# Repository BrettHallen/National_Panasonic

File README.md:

# National/Panasonic
Information about National/Panasonic computers.

## [National JR-200](/National_JR-200)

## [National CF-3000](/National_CF-3000)
The MSX1 compatible computer.<br>

Machines in the range:<br>
- National CF-2000 (all-in-one)
- National CF-2601 (Superimposition Unit)
- National CF-3000 (separate keyboard)
- National CF-3300 (with additional 3.5" floppy drive)

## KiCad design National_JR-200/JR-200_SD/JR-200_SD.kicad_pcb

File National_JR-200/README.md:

# National JR-200
Information about the National/Panasonic JR-200 computer.<br>

It was exported to the US as the JR-200U and Europe as the JR-200UP (PAL).<br>

# Troubleshooting Φ2 Clock
My first JR-200 doesn't work - the Φ2 is currently missing.

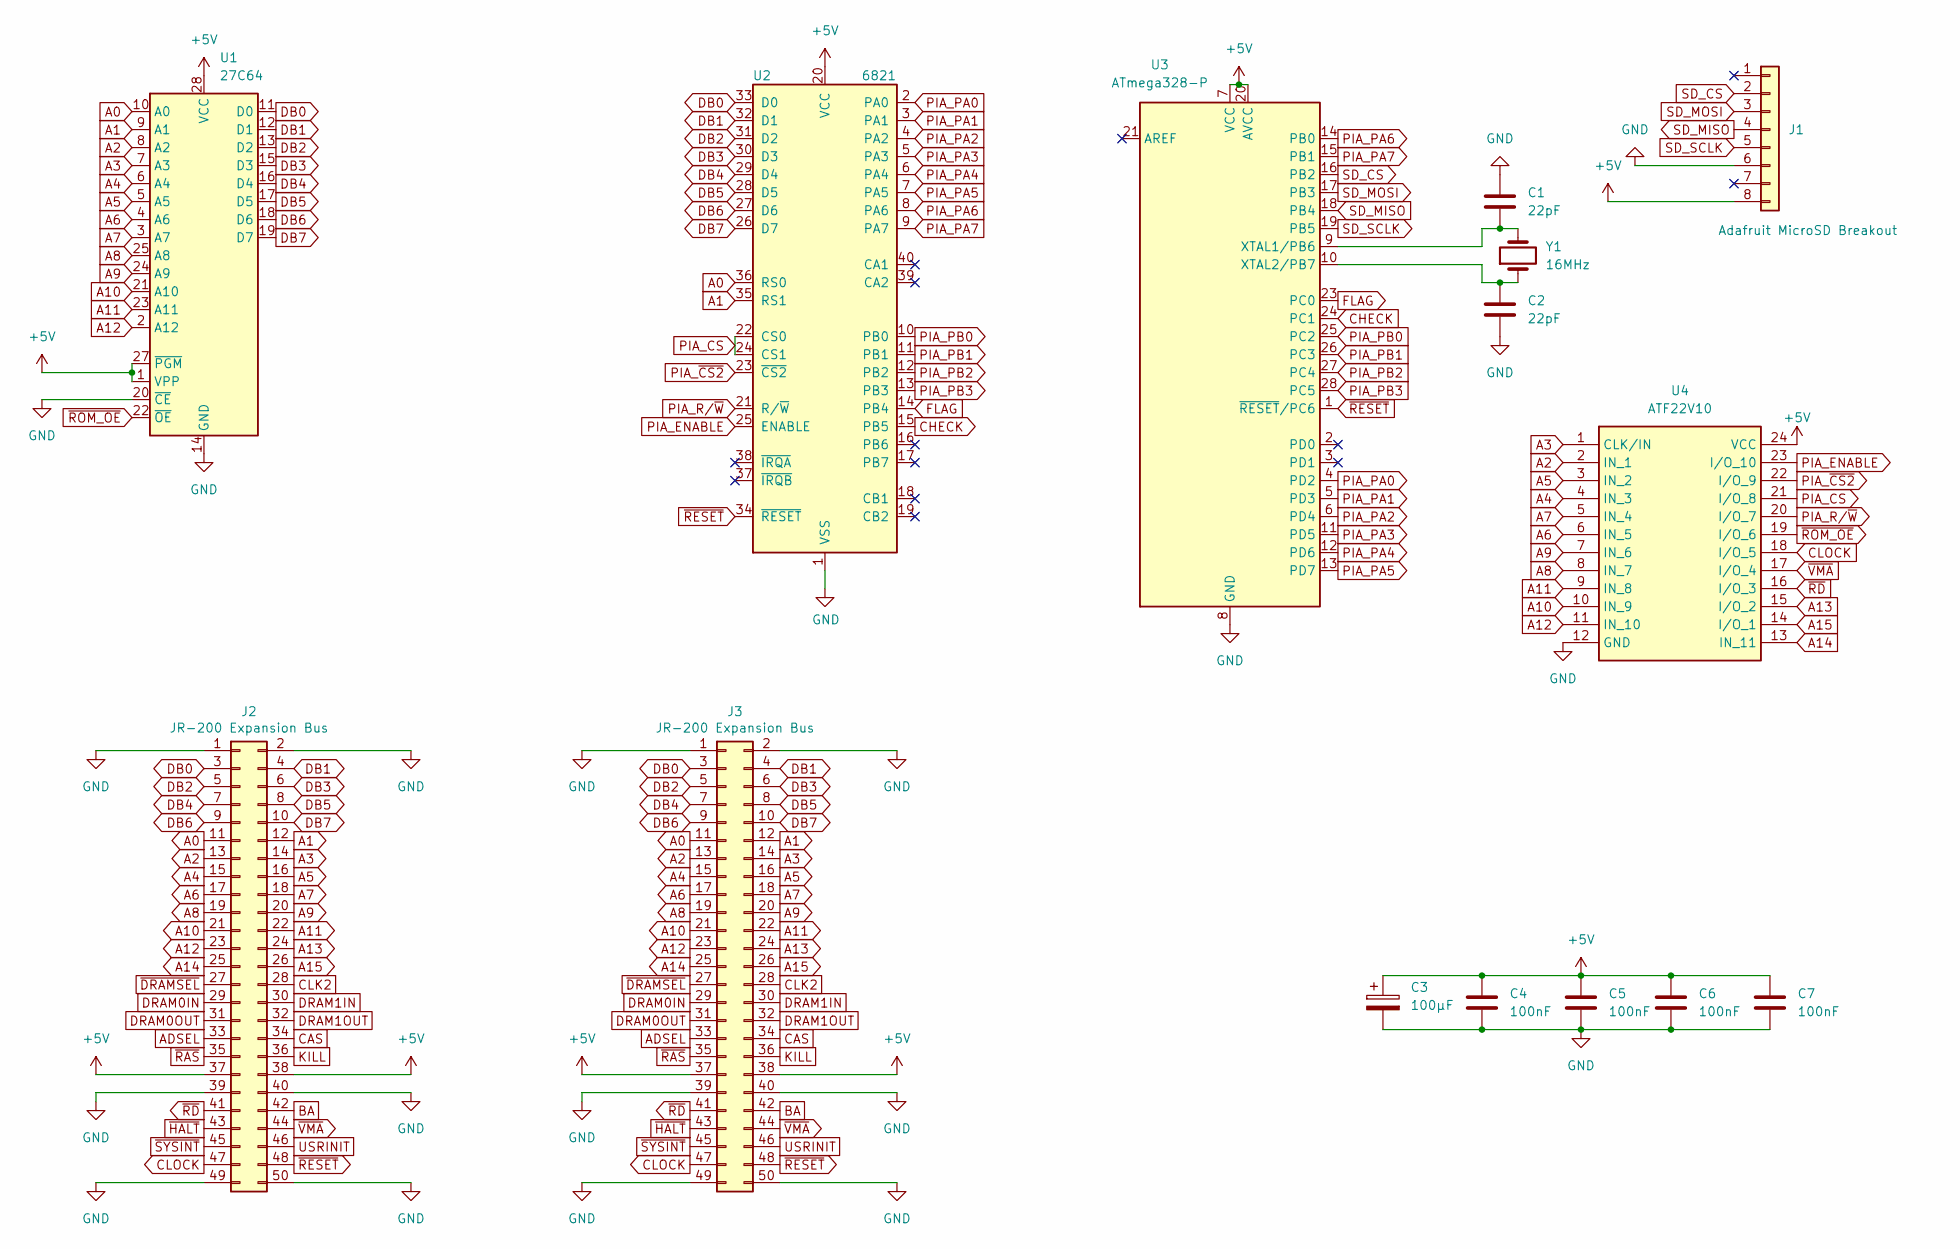
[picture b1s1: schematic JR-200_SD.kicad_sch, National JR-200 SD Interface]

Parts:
C1, C2: 22pF; C_Disc_D3.8mm_W2.6mm_P2.50mm
C3: 100µF; CP_Radial_D5.0mm_P2.50mm
C4, C5, C6, C7: 100nF; C_Disc_D3.8mm_W2.6mm_P2.50mm
J1: Adafruit MicroSD Breakout
J2, J3: JR-200 Expansion Bus; PinHeader_2x25_P2.54mm_Vertical
U1: 27C64; DIP-28_W15.24mm
U2: 6821; DIP-40_W15.24mm_LongPads
U3: ATmega328-P; DIP-28_W7.62mm
U4: ATF22V10; DIP-24_W7.62mm; Mouser Part Number 556-AF750CL15PU
Y1: 16MHz; Crystal_HC49-U_Vertical

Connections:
+5V: C3.1, C4.1, C5.1, C6.1, C7.1, J1.8, J2.37, J2.38, J3.37, J3.38, U1.1 (VPP), U1.27 (~PGM), U1.28 (VCC), U2.20 (VCC), U3.7 (VCC), U3.20 (AVCC), U4.24 (VCC)
A0: J2.11, J3.11, U1.10 (A0), U2.36 (RS0)
A1: J2.12, J3.12, U1.9 (A1), U2.35 (RS1)
A2: J2.13, J3.13, U1.8 (A2), U4.2 (IN_1)
A3: J2.14, J3.14, U1.7 (A3), U4.1 (CLK/IN)
A4: J2.15, J3.15, U1.6 (A4), U4.4 (IN_3)
A5: J2.16, J3.16, U1.5 (A5), U4.3 (IN_2)
A6: J2.17, J3.17, U1.4 (A6), U4.6 (IN_5)
A7: J2.18, J3.18, U1.3 (A7), U4.5 (IN_4)
A8: J2.19, J3.19, U1.25 (A8), U4.8 (IN_7)
A9: J2.20, J3.20, U1.24 (A9), U4.7 (IN_6)
A10: J2.21, J3.21, U1.21 (A10), U4.10 (IN_9)
A11: J2.22, J3.22, U1.23 (A11), U4.9 (IN_8)
A12: J2.23, J3.23, U1.2 (A12), U4.11 (IN_10)
A13: J2.24, J3.24, U4.15 (I/O_2)
A14: J2.25, J3.25, U4.13 (IN_11)
A15: J2.26, J3.26, U4.14 (I/O_1)
ADSEL: J2.33, J3.33
BA: J2.42, J3.42
CAS: J2.34, J3.34
CHECK: U2.15 (PB5), U3.24 (PC1)
CLK2: J2.28, J3.28
CLOCK: J2.47, J3.47, U4.18 (I/O_5)
DB0: J2.3, J3.3, U1.11 (D0), U2.33 (D0)
DB1: J2.4, J3.4, U1.12 (D1), U2.32 (D1)
DB2: J2.5, J3.5, U1.13 (D2), U2.31 (D2)
DB3: J2.6, J3.6, U1.15 (D3), U2.30 (D3)
DB4: J2.7, J3.7, U1.16 (D4), U2.29 (D4)
DB5: J2.8, J3.8, U1.17 (D5), U2.28 (D5)
DB6: J2.9, J3.9, U1.18 (D6), U2.27 (D6)
DB7: J2.10, J3.10, U1.19 (D7), U2.26 (D7)
DRAM0IN: J2.29, J3.29
DRAM0OUT: J2.31, J3.31
DRAM1IN: J2.30, J3.30
DRAM1OUT: J2.32, J3.32
FLAG: U2.14 (PB4), U3.23 (PC0)
GND: C1.1, C2.2, C3.2, C4.2, C5.2, C6.2, C7.2, J1.6, J2.1, J2.2, J2.39, J2.40, J2.49, J2.50, J3.1, J3.2, J3.39, J3.40, J3.49, J3.50, U1.14 (GND), U1.20 (~CE), U2.1 (VSS), U3.8 (GND), U3.22 (GND), U4.12 (GND)
KILL: J2.36, J3.36
unnamed: C1.2, U3.9 (XTAL1/PB6), Y1.2
unnamed: C2.1, U3.10 (XTAL2/PB7), Y1.1
PIA_CS: U2.22 (CS0), U2.24 (CS1), U4.21 (I/O_8)
PIA_ENABLE: U2.25 (ENABLE), U4.23 (I/O_10)
PIA_PA0: U2.2 (PA0), U3.4 (PD2)
PIA_PA1: U2.3 (PA1), U3.5 (PD3)
PIA_PA2: U2.4 (PA2), U3.6 (PD4)
PIA_PA3: U2.5 (PA3), U3.11 (PD5)
PIA_PA4: U2.6 (PA4), U3.12 (PD6)
PIA_PA5: U2.7 (PA5), U3.13 (PD7)
PIA_PA6: U2.8 (PA6), U3.14 (PB0)
PIA_PA7: U2.9 (PA7), U3.15 (PB1)
PIA_PB0: U2.10 (PB0), U3.25 (PC2)
PIA_PB1: U2.11 (PB1), U3.26 (PC3)
PIA_PB2: U2.12 (PB2), U3.27 (PC4)
PIA_PB3: U2.13 (PB3), U3.28 (PC5)
PIA_R/~W: U2.21 (R/~W), U4.20 (I/O_7)
PIA_~CS2: U2.23 (~CS2), U4.22 (I/O_9)
SD_CS: J1.2, U3.16 (PB2)
SD_MISO: J1.4, U3.18 (PB4)
SD_MOSI: J1.3, U3.17 (PB3)
SD_SCLK: J1.5, U3.19 (PB5)
USRINIT: J2.46, J3.46
~DRAMSEL: J2.27, J3.27
~HALT: J2.43, J3.43
~RAS: J2.35, J3.35
~RD: J2.41, J3.41, U4.16 (I/O_3)
~RESET: J2.48, J3.48, U2.34 (~RESET), U3.1 (~RESET/PC6)
~ROM_OE: U1.22 (~OE), U4.19 (I/O_6)
~SYSINT: J2.45, J3.45
~VMA: J2.44, J3.44, U4.17 (I/O_4)

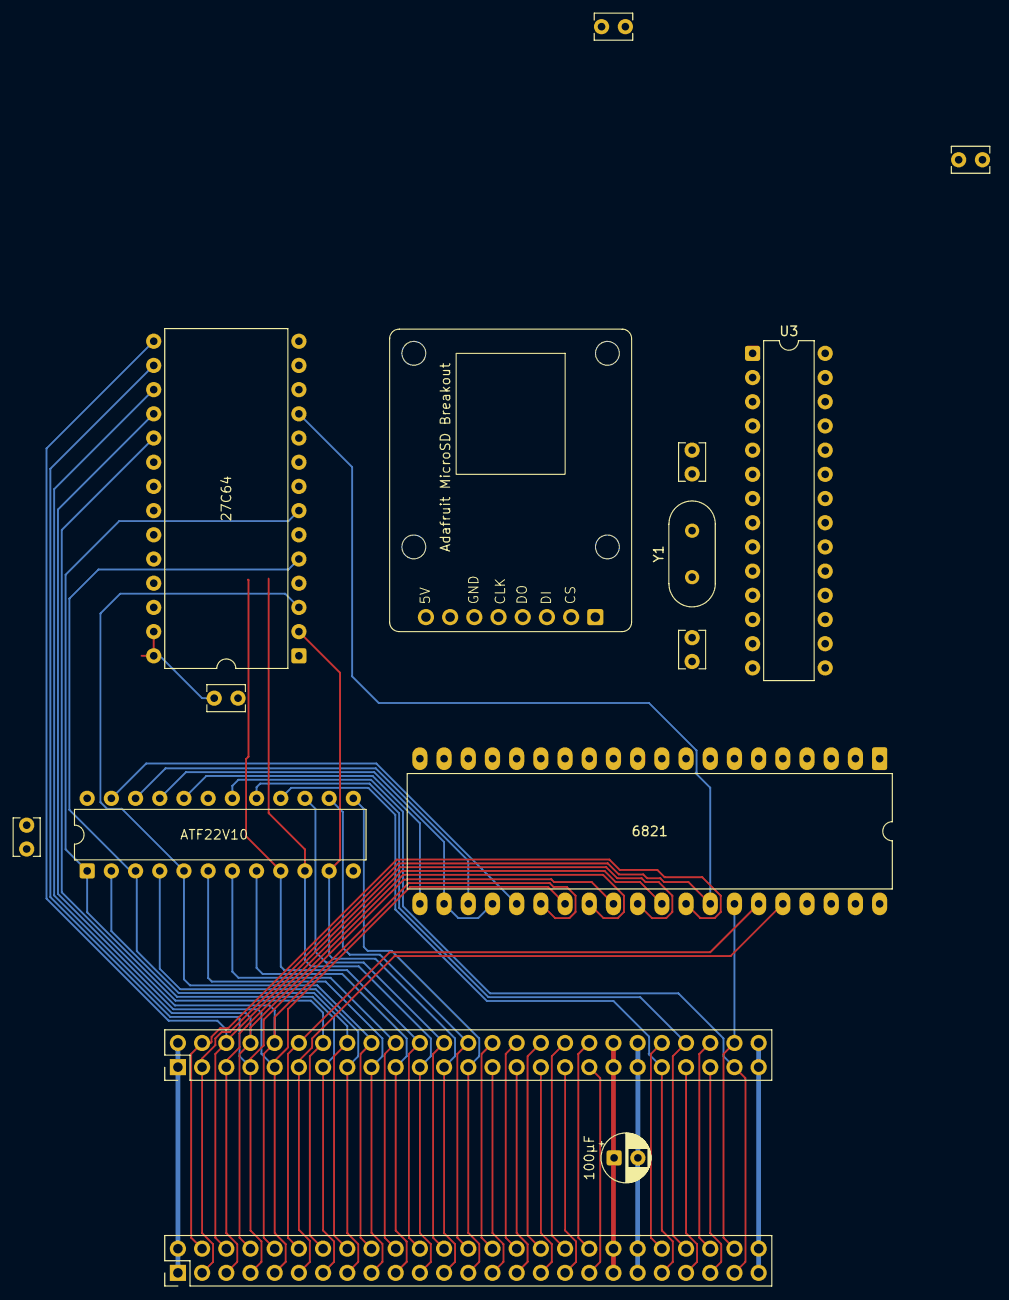
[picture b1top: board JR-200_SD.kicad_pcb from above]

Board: 2 copper layers, 15 parts (0 on the bottom side), 69 nets.

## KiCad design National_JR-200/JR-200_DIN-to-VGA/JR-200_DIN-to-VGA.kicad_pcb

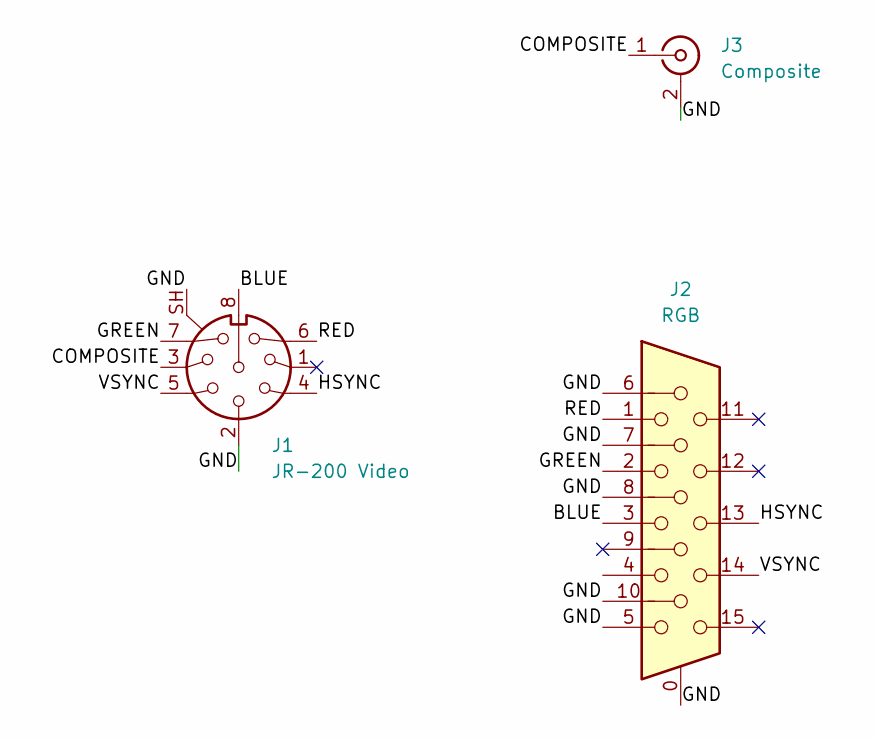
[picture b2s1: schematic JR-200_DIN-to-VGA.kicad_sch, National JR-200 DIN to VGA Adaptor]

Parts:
J1: JR-200 Video; SDF80J
J2: RGB; DSUB-15-HD_Socket_Horizontal_P2.29x2.54mm_EdgePinOffset8.35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
J3: Composite; 1560099E

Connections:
/BLUE: J1.8, J2.3
/COMPOSITE: J1.3, J3.1 (In)
/GND: J1.2, J1.SH, J2.0, J2.5, J2.6, J2.7, J2.8, J2.10, J3.2 (Ext)
/GREEN: J1.7, J2.2
/HSYNC: J1.4, J2.13
/RED: J1.6, J2.1
/VSYNC: J1.5, J2.14

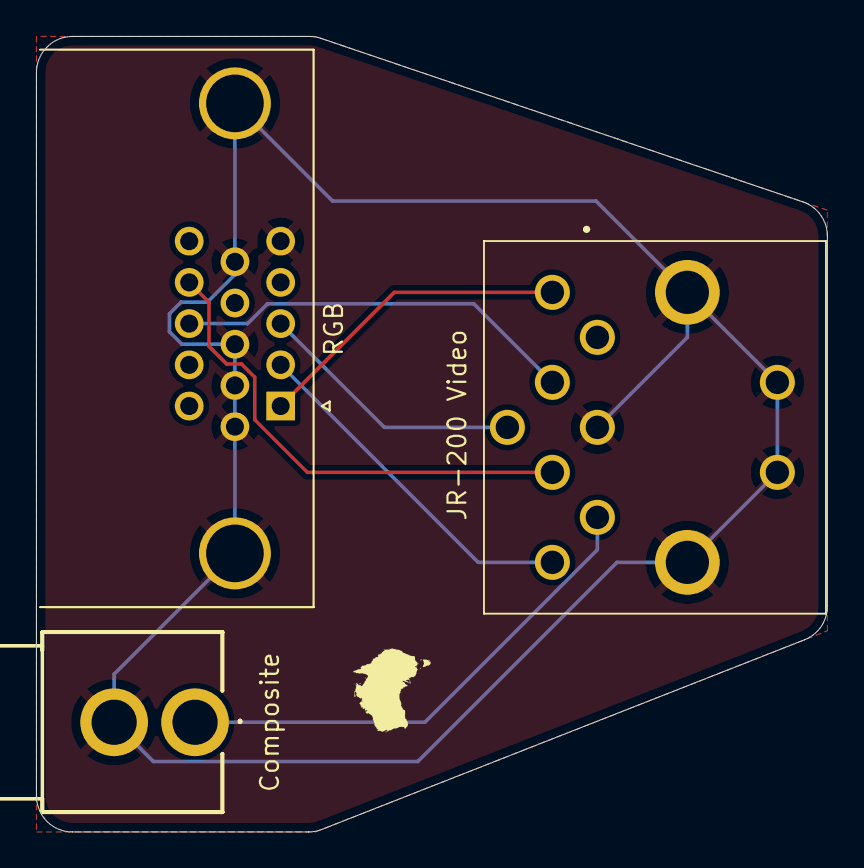
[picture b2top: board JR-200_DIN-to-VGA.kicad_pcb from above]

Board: 2 copper layers, 43.9 x 44.2 mm, 3 parts (0 on the bottom side), 7 nets.

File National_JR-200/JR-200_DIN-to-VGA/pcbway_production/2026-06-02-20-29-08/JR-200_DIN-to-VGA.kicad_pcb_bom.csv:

Designator,Quantity,Value,Footprint,Package,MPN,DNP,Mount_Type,Description
J1,1,JR-200 Video,SDF80J,,,,tht,
J2,1,RGB,DSUB-15-HD_Socket_Horizontal_P2.29x2.54mm_EdgePinOffset8.35mm_Housed_MountingHolesOffset10.89mm,,,,tht,"15-pin D-SUB connector, socket (female), High density (3 columns), Triple Row, Generic, VGA-connector, Mounting Hole"
J3,1,Composite,1560099E,,,,tht,"coaxial connector (BNC, SMA, SMB, SMC, Cinch/RCA, LEMO, ...)"

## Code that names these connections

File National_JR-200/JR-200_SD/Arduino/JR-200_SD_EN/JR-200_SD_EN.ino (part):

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/* 
ATmega328  Connection
--------------------
PB0        PIA PA6 (PIA_PA6)
PB1        PIA PA7 (PIA_PA7)
PB2        SD CS (CABLESELECTPIN)
PB3        SD MOSI
PB4        SD MISO
PB5        SD SCK
PC0        PIA PB4 (FLAGPIN)
PC1        PIA PB5 (CHKPIN)
PC2        PIA PB0 (PIA_PB0)
PC3        PIA PB1 (PIA_PB1)
PC4        PIA PB2 (PIA_PB2)
PC5        PIA PB3 (PIA_PB3)
PD2        PIA PA0 (PIA_PA0)
PD3        PIA PA1 (PIA_PA1)
PD4        PIA PA2 (PIA_PA2)
PD5        PIA PA3 (PIA_PA3)
PD6        PIA PA4 (PIA_PA4)
PD7        PIA PA5 (PIA_PA5)
*/
#define CABLESELECTPIN  (10)
#define CHKPIN          (15)
#define PIA_PA0          (2)
#define PIA_PA1          (3)
#define PIA_PA2          (4)
#define PIA_PA3          (5)
#define PIA_PA4          (6)
#define PIA_PA5          (7)
#define PIA_PA6          (8)
#define PIA_PA7          (9)
#define FLAGPIN         (14)
#define PIA_PB0         (16)
#define PIA_PB1         (17)
#define PIA_PB2         (18)
#define PIA_PB3         (19)

#define SD_STATUS_OK             0x00
#define SD_STATUS_INIT_ERROR     0xF0
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// pin10 output
  pinMode(CABLESELECTPIN,OUTPUT);
  pinMode( CHKPIN,INPUT);  // CHK
  pinMode( PIA_PA0,OUTPUT); // 送信データ ... transmit data
  pinMode( PIA_PA1,OUTPUT); // 送信データ
  pinMode( PIA_PA2,OUTPUT); // 送信データ
  pinMode( PIA_PA3,OUTPUT); // 送信データ
  pinMode( PIA_PA4,OUTPUT); // 送信データ
  pinMode( PIA_PA5,OUTPUT); // 送信データ
  pinMode( PIA_PA6,OUTPUT); // 送信データ
  pinMode( PIA_PA7,OUTPUT); // 送信データ
  pinMode( FLAGPIN,OUTPUT);  // flag

  pinMode( PIA_PB0,INPUT_PULLUP); // 受信データ ... receive data
  pinMode( PIA_PB1,INPUT_PULLUP); // 受信データ
  pinMode( PIA_PB2,INPUT_PULLUP); // 受信データ
  pinMode( PIA_PB3,INPUT_PULLUP); // 受信データ

  digitalWrite(PIA_PA0,LOW);
  digitalWrite(PIA_PA1,LOW);
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
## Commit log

2026-06-27 Moved from National_JR-200 repository
2026-06-27 Updated file paths
